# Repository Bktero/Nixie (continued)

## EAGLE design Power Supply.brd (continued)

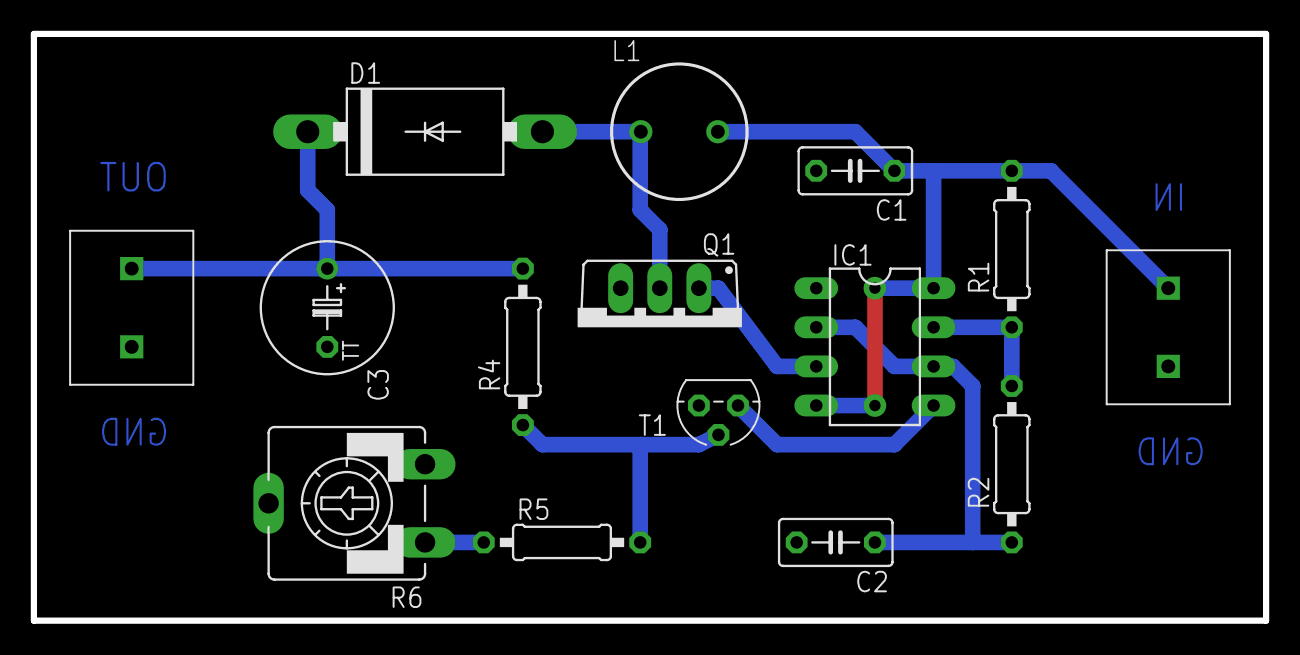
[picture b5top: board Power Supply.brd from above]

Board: 2 copper layers, 80.0 x 38.1 mm, 15 parts (0 on the bottom side), 10 nets.

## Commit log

2015-03-09 Share
    Share Eagle project with power supply board
    Change name in LICENSE
2015-07-07 Change license, update readme
2015-12-22 Control Logic
    1 Hz signal generator
2015-12-22 Ignore Eagle's backup files
    See
    https://www.cadsoftusa.com/fileadmin/journalist/Documents/TUTORIAL-part1
    _Introduction-of-the-Control-Panel_v6.pdf
    « EAGLE creates a number of backup files each time you save your
    project. There is a maximum of 9 possible backups. They are named with
    the file extension .b#1 to .b#9 for the board file (*.brd). The same
2016-01-06 Create tube schematics
2016-01-06 Create tube board
2016-01-06 Starting routing
2016-01-06 Keep routing
2016-01-07 Complete schematics
2016-01-10 Add TubeAlt, rename Control Logic, use jumper
2016-02-04 Separate board for time reference generator
2016-02-04 Rename files
2016-02-17 Ajouter des capa de decouplage + augmentation isolation des thermals
2016-02-17 Ajout simulation avec LTSpiceIV pour le controle des secondes
2016-02-18 Add minutes to simulation
2016-02-23 Remove unnecessary reset signals of seconds (unit) and minutes (units)
2016-02-25 Square to pulse simulation
2016-02-25 Hour simulation
2016-03-06 Add/modify description of schematics
2016-03-07 Create 'Nixie Clock' and delete previous attempts with tubes
2016-03-07 Replace "dxxx" with "txxx"
2016-03-10 Uncompleted schematics for the Nixie Clock and simulation for AND with diodes
2016-03-11 Start routing for tubes board
2016-03-11 Fix MSPA42 and IN-14 packages
2016-03-13 Group components per digit
2016-03-13 Pack layout
2016-03-13 Pack more
2016-03-13 Complete schematics and finish placing components
2016-03-14 Complete layout of control signals for 4017s
2016-03-14 Complete layout for 4017's outputs
2016-03-19 Set isolation of the ground plane
2016-03-20 Rearrange transistors to avoid routes between the tubes' pins
2016-03-21 Re-Add CD4081 in simulation
2016-03-21 Add neon lamps
2016-03-21 All Routed \o/
2016-05-02 Add mouting holes
2016-05-02 Increase size for pads and vias
2016-05-02 Add visible dimensions on PCB
2016-05-12 Add VCC text on PCB
2016-05-18 Change message from Vcc to VDD
2016-05-18 Add ground plane on top layer and increase via size
2016-05-19 Change route width and ground plane isolation
    There are some high voltage signal on the top layer. These signals need
    wide routes and the ground plane that surround them need an important
    isolation.
2016-05-19 Increase pad size
2016-05-20 Use an alternative package for tubes, with bigger pads
2016-05-20 Fix isolation issues and reduce pads size because some pins got disconnected
2016-07-02 Fix RESET_HOURS signal in simulation
2016-07-02 Fix RESET_HOURS signal in schematics and layout
2016-07-11 Fix RESET_HOURS signal in schematics and layout (bis)
2016-07-11 Fix layout by adding missing route
